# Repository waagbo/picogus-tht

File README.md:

# PicoGUS THT

PicoGUS is a Raspberry Pi Pico based ISA sound card for DOS and Win9x retro computers
It is a highly versatile clone card that provides near perfect emulation of the Gravis Ultrasound, Sound Blaster-series, AdLib, Tandy 3-voice and CMS/Game Blaster.

Additional features like CD-ROM (Panasonic MKE), MPU-401 and USB game controllers build further on the cards versatility and the wavetable header will further extend the capacity with a card like [X2GS from Serdaco](https://serdashop.com/products/x2gs-te) to get the original Roland magic or even a [WavetablePi](https://github.com/scrapcomputing/WavetablePiHoriz) for the ultimate all-in-one experience for MS-DOS games. 

**PicoGUS THT is a through-hole conversion of the [PicoGUS project](https://github.com/polpo/picogus).**<br />
The conversion introduces through-hole components where possible in addition to embedding new features and ideas while still keeping the card compatible with the upstream project. The design goal is to make the project be easier to solder by hand as well as giving it a higher level of retro asthetics.

PicoGUS THT exists in multiple variants based on different PicoGUS revisions. Each variant is found in their separate folder (or branch if still experimental). The different *hw* designs feature additional documentation including ready to order BOM CSVs in their respective *docs* folders.

The designs still have some TSSOP SMD chips as they do not have THT equivalents, namely the two *SN74CB3T3257PWR* level shifters (U3/U4) as well as the PCM510xA DAC. PicoGUS THT features a redesigned footprint to ease debugging in case something goes wrong.

**Note!** The hardware revisions are intentionally kept aligned with the *major* revision as the original PicoGUS boards. This is done to indicate hardware feature compatibility and to prevent confusion in case of any future major revisions of the original PicoGUS design.

### Version 1.3

This version is an extension of the PicoGUS 1.2 design while implementing the *wavetable header* with manual volume control from the *hw-hand386* branch. Together with the addition of a full size USB-A connector accessible from the computers backside this card is now a real competitor to the v2.0 SMD design.

In addition, the THT boards have also been slightly resized to optimize for component placement and JCLPCB-pricing.
The v1.3.2 has been successfully built by hand and the following features have been tested and verified.
The following features have been tested and verified.
* [x] Card Assembly ➔ OK, with minor adjustments to DigiKey BOM.
* [x] Flash, boot and detect card ➔ OK (v4.2.0-beta2).
* [x] Audio Playback ➔ OK (v4.2.0-beta2, SB Mode).
* [x] MIDI Playback (Wavetable Connector) ➔ OK (WavetablePi)
* [ ] MIDI Playback (External 3.5mm Jack)
* [x] USB-A Connector (Both CD-ROM and experimental PGDFS filesystem) ➔ OK

Assembly should be *EASY to MEDIUM* with the appropriate quality tools and consumables and a good project for beginners that want a little more challenge. Here is a list of recommended supplies with some personal recommendations:
* [Low Temperature Solder Paste](https://www.digikey.com/en/products/detail/chip-quik-inc/NC191LTA10/13531404) for easy soldering of SMD components.
* [Flux](https://www.digikey.com/en/products/detail/chip-quik-inc/NC191-2CC6/11480375) as it makes solder behave like magic when you need it the most.
* [Solder Wick](https://www.digikey.com/en/products/detail/chemtronics/SW14035/5177685) as it will help you when flux can't. Remember to **NEVER** pull a stuck wick.
* [Soldering Iron with J-Tip (Alientek T90B)](https://www.aliexpress.com/item/1005010015046346.html) will make the SMD components a breeze to solder. 
* [Tweezers](https://www.aliexpress.com/item/1005007298021096.html) for handling the SMD components.
* Digital Microscope of decent quality from AliExpress is very useful for visual inspection of SMD chips.
* Multimeter with good continuity tester.

#### User Build Gallery
|<br>waagbo|<br>|<br>|<br>|
|-|-|-|-|
| | | | |

### Version 2.1

This is an experimental extension of the PicoGUS 2.0 SMD design, made possible using a Waveshare Core2350B board to free enough I/O ports for the 2.0 feature set. This is still in the design phase.
<br/>

### Experimental Firmware
We have added experimental features that adds upon community ideas on top of the original firmware and software components. The features are submitted as Pull Requests to the original PicoGUS repository as well but there is no guarantee that they will ever be included in the official software releases:
* DFS drive support inspired by PicoMEM so the USB drive can be accessed from MS-DOS.
* CD images in a `CDROM` folder on the USB drive.
* A web page on boards with a Pico W or Pico 2 W: status, volumes, settings, mode switching, mt32-pi control and firmware updates from a browser.

The experimental features live on their own branches and are built into a separate *experimental* set of firmware and DOS tools next to the regular one, see [sw/experimental](sw/experimental/README.md).

### RP2350 Firmware
The firmware builds for the RP2350 as well as the RP2040, from the same source: for the v1.x boards with a Raspberry Pi Pico 2 (W) instead of a Pico (W), and for the v2.1 board's Core2350B module. Releases contain the firmware for both microcontrollers. See [RP2350 support](sw/docs/rp2350.md) for the firmware files, how to build them and what is left to test on hardware.

<br/>

**A big thank you to [Ian Scott (polpo)](https://github.com/polpo/) for the PicoGUS design and his contributions to the retro community.**<br/>**May his work set an example for future open-source hardware projects.**

--<br/>
Vidar Waagbø, Retro City AS

## PicoGUS

The original PicoGUS project is found at [polpo/pigocus](https://github.com/polpo/picogus) or www.picogus.com.<br/>
Here are the original README.md to give some more information about the great features of the PicoGUS:

ISA sound card and CD-ROM drive emulation on the Raspberry Pi Pico's RP2040 microcontroller. PicoGUS can emulate:

* [Gravis Ultrasound (GUS)](https://en.wikipedia.org/wiki/Gravis_Ultrasound) - the primary focus of PicoGUS, hence the name
* [Sound Blaster 16](https://en.wikipedia.org/wiki/Sound_Blaster_16) (OPL3) / [Sound Blaster Pro 2](https://en.wikipedia.org/wiki/Sound_Blaster#Sound_Blaster_Pro_2,_CT1600) (OPL3) / [AdLib](https://en.wikipedia.org/wiki/Ad_Lib,_Inc.) (OPL2)
* [MPU-401 (with intelligent mode)](https://en.wikipedia.org/wiki/MPU-401) - outputs MIDI data on 3.5mm MIDI TRS connector
* [Tandy 3-voice](http://www.vgmpf.com/Wiki/index.php?title=Tandy_3_Voice)
* [CMS/Game Blaster](http://nerdlypleasures.blogspot.com/2012/10/all-you-ever-wanted-to-know-about.html)
* [Game port joystick](https://en.wikipedia.org/wiki/Game_port)
* [Panasonic/MKE CD-ROM](https://en.wikipedia.org/wiki/Panasonic_CD_interface)

Current status: perpetual beta! See the [main wiki page](https://github.com/polpo/picogus/wiki) for current status and the [compatibility list](https://github.com/polpo/picogus/wiki/Compatibility-list) for support status of various DOS programs and other system compatibility notes. This project has a heavy demoscene focus due to the GUS's history so that's what I've concentrated on, but GUS support in games is very good to excellent.

Want to buy a PicoGUS? Fully assembled PicoGUS 2.0 sound cards are available from these sources, all of whom ship worldwide:

* [Joe's Computer Museum Shop](https://jcm-1.com/product/picogus-v2/) - in US 🇺🇸
* [Serdashop](https://www.serdashop.com/PicoGUS) - in EU 🇪🇺
* [Flamelily IT](https://shop.flamelily.co.uk/picogus) - in UK 🇬🇧

Want to make your own PicoGUS? See the [build guide](https://github.com/polpo/picogus/wiki/Building-your-PicoGUS). Note that the more DIY friendly v1.1.1 hardware has some documented issues with reset – a forthcoming v1.2 revision will fix these issues. **Important caveat**: due to the specs of the Pico, assumptions made by programs written to use the GUS, the imprecise nature of emulation, and the varying specs of retro DOS PC hardware, some things will likely never be perfect. **This is still a work in progress.**

Have a PicoGUS and want to use it? See the [configuring and using your PicoGUS guide](https://github.com/polpo/picogus/wiki/Configuring-and-using-your-PicoGUS).

Want to support PicoGUS? I have a limited number of machines to test PicoGUS in and donating either money or motherboards would be greatly appreciated and help increase the compatibility of PicoGUS.

You can donate via [PayPal](https://paypal.me/ianpolpo) or Ko-Fi: 

See/hear PicoGUS in action on YouTube:

Videos by others:

My videos:

## Open Source Credits

* [Raspberry Pi Pico C/C++ SDK](https://github.com/raspberrypi/pico-sdk)
* `pico_audio_i2s` from [pico-extras](https://github.com/raspberrypi/pico-extras)
* `stdio_async_uart` from [PicoCart64](https://github.com/kbeckmann/PicoCart64)
* `gus-x.cpp` adapted from [DOSBox-X](https://github.com/joncampbell123/dosbox-x)
* OPL/AdLib emulation from [rp2040-doom](https://github.com/kilograham/rp2040-doom) (based on [emu8950](https://github.com/digital-sound-antiques/emu8950))
* MPU-401 emulation adapted from [HardMPU](https://github.com/ab0tj/HardMPU) and [DOSBox-X](https://github.com/joncampbell123/dosbox-x)
* Tandy 3-voice emulation based on code contributed by [Aaron Giles](https://aarongiles.com/), adapted from [DREAMM](https://aarongiles.com/dreamm/) 
* CMS emulation based on code contributed by [Aaron Giles](https://aarongiles.com/), adapted from [DREAMM](https://aarongiles.com/dreamm/)
* USB support uses [TinyUSB](https://github.com/hathach/tinyusb) and [tusb_xinput](https://github.com/Ryzee119/tusb_xinput) with USB mass storage improvements by rppicomidi and wbcbz7.
* FAT drive support by [FatFS](https://elm-chan.org/fsw/ff/)

## License

The hardware portions of this repository (hw/ directory) are licensed under the CERN OHL version 2, permissive.

The software portions of this repository (sw/, pgusinit/ directories) as a collection are licensed under the GNU GPL version 2. Some files are individually dual-licensed under BSD or MIT licenses – see the license in the file headers for details.

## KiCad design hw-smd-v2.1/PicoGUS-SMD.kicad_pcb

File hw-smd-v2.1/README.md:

# PicoGUS SMD v2.1 – the THT v2.1 card with surface-mount parts

The SMD counterpart of [PicoGUS THT v2.1](../hw-tht-v2.1/README.md), in the way [`hw-smd`](../hw-smd/README.md) is the
SMD counterpart of THT v1.3. It is **the same circuit with the same reference designators and the same nets**, so the
THT v2.1 README describes how it works and the same firmware runs on it (`core2350.uf2`, and `pg-ne2k-v21.uf2` with
the radio module). Only the packages change.

* Same card: the 102.0 × 99.95 mm outline, the bracket-side connectors and tab holes of THT v2.1, 4 layers.
* **Same Core2350B arrangement**: the Waveshare Core2350B2 module on four 2x8 sockets, same footprint and same place.
* **Parts picked for soldering by hand**: 0805 resistors and capacitors on KiCad's hand-solder lands (longer pads),
  SOIC (1.27 mm pitch) wherever the chip exists as SOIC, and everything on the front. Nothing is on the back.
* The radio module (U14) and the experimental boot ROM (U15–U17) of THT v2.1 are included, and optional as there.
  The boot ROM's flash keeps its through-hole socket, and as on THT v2.1.1 it can be written in the card: see
  [Boot ROM socket](#boot-rom-socket).
* **Every joint can be made with a soldering iron.** That rules parts out whose leads hide under the body.

> **Status: draft for placement review. The schematic is done; the board has every part placed and labelled but is
> NOT routed. Not built, not tested.**
> The files say **v2.1.1** (2026-11-27), like THT v2.1.1 whose circuit they follow: the flash's write enable is on
> ISA's memory write strobe.
> Schematic: ERC gives the same messages as THT v2.1.1, and its netlist is identical to THT v2.1.1's (201 nets, 589
> pins, 102 parts; only footprints, values and part numbers differ). Board: 0 courtyard overlaps, 0 schematic parity
> issues, 398 connections still to route. The BOM has part numbers but no prices: see [BOM](#bom).
> The board is not in the Hardware workflow yet, because an unrouted board fails its DRC.

| File | What |
|---|---|
| `PicoGUS-SMD.kicad_pro/.kicad_sch/.kicad_pcb/.kicad_dru` | KiCad **10** project. The board is the THT v2.1 board (outline, stackup, plane zones, logo, edge connector, connectors and modules in place) with the SMD parts placed and no tracks |
| `audio.kicad_sch`, `mixer.kicad_sch`, `bootrom.kicad_sch` | The DAC, line-out mixer and boot ROM sheets of THT v2.1 with SMD footprints |
| `PicoGUS-SMD-schematic.pdf` | Schematic PDF |
| `docs/BOM-SMD.csv` | BOM with part numbers, no prices yet: see [BOM](#bom) |
| `docs/renders/` | Render of the placement |
| `tools/gen_tssop20_handsolder.py` | Writes the footprint this board adds to the shared library (`hw-common/PiGUS library.pretty`): the TSSOP-20 with hand-solder toes and no test pads |

## What changed from THT v2.1

| Part | THT v2.1 | SMD v2.1 |
|---|---|---|
| U3 74AHC14, U4/U5 74AHC00, U6 74AHCT126 | DIP-14 | SOIC-14 |
| U7 74AHC244 | DIP-20 | SOIC-20 wide |
| U11 NE5532 | DIP-8 | SOIC-8 |
| U9 MCP1826S 3.3 V regulator | TO-220, lying | SOT-223 |
| U16 74HCT138, U17 74HCT153 (boot ROM) | TSSOP-16 on the back | SOIC-16 on the front |
| U10 PCM5100A | TSSOP-20 with hand-solder toes and a test pad per pin | the same toes, no test pads |
| Resistors | axial; four 0805 on the back | 0805 on the front; 0.1 % thin film in the audio path (R10, R11, R21–R26), 1 % thick film elsewhere |
| Capacitors up to 2.2 µF | radial ceramic | 0805: X7R, and C0G for the DAC filter (C21, C22) and the mixer feedback (C24, C25) |
| 10 µF (C11–C13, C17, C47) | radial ceramic | 1206 |
| 47 µF and 100 µF (C1, C28, C29, C38) | radial electrolytic | SMD can, 6.3 mm |
| C39–C42, 2.2 µF Waveblaster coupling | film | bipolar SMD electrolytic, 4 mm can (as `hw-smd` does for the same job) |
| FB1–FB4 | axial ferrite | 0805 ferrite bead |
| D2, D3 | 1N5819, DO-41 | B5819W, SOD-123 |
| D1 | 3 mm LED | 0805 LED |
| F1 | radial PTC | 1812 PTC |
| SW1, SW2 | 6 mm through-hole button | 6 mm SMD button |

Unchanged: U1/U2 (SN74CB3T3257) exist only as TSSOP and keep THT v2.1's footprint with hand-solder toes and a test
pad per pin; U13 (M62429L) is a SOIC-8 already. All connectors and headers stay through hole, as do the module
sockets and the PLCC-32 socket of the boot ROM. The radio module keeps its hand-solder lands.

## Placement

The connectors, the module, the DAC, the mixer and the power parts are where THT v2.1 has them. The logic and the
boot ROM are grouped differently, because the small packages allow it:

* **ISA logic** (U3, U4, U5, U6 and U7): a 2 × 2 block of the SOIC-14s in the centre of the card, between the DAC and
  the bus switches, with U7 below it. On THT v2.1 the DIPs fill a column down the left edge, far from the edge
  connector pins, the jumper block and the module they connect. Measured as the straight-line length of the
  connections of these five chips (shortest tree per net, supplies left out):

  | Arrangement | Length | |
  |---|---|---|
  | Column on the left, as on THT v2.1 | 1773 mm | |
  | The same column with the chips in another order or turned 180° | 1766 mm at best | turning or reordering gains nothing |
  | The column closed up at its lower end (capacitors beside the chips) | 1690 mm | −5 % |
  | **Block in the centre (this placement)** | **1455 mm** | **−18 %** |

  For all signal nets of the card that is 4621 mm before and 4367 mm now. Each chip is turned so that its supply
  pin is at the bottom right, and its 0.1 µF capacitor stands right of it at that pin; that orientation costs 38 mm
  against the best one. The pull-ups and the pull-down (R5, R18, R1) stand left of the block. The left third of the
  card under the Waveblaster header is empty now.
* **Boot ROM**, bottom left: the flash socket where THT v2.1 has it, the address select U17 above it and the decoder
  U16 right of it.
* **Power**: the regulator U9 with its input and output capacitors against its pins, then the two supply diodes in a
  row that ends at the module's supply pin.
* **DAC**: see [DAC capacitors](#dac-capacitors). The AVDD bulk capacitor C38 is next to the bead that feeds AVDD
  (on THT v2.1 it is beside the mixer).
* **Mixer**: the feedback resistor and capacitor of each channel beside the op-amp pins they connect, the input
  resistors below them, the ±12 V filters above and below.
* **Waveblaster volume**: U13 is turned a quarter so both channels face the mixer, and all four coupling capacitors
  are at the chip. On THT v2.1 the two input capacitors are more than 30 mm away, near the header, which leaves a
  long high-impedance track. The input pull-downs R31/R32 moved here with them.
* The analogue parts stay inside THT v2.1's AGND and AVDD plane islands, which are unchanged; the logic block is
  outside them.

Neighbouring parts have at least 0.55 mm between their pads. Every part has its reference on the silkscreen beside
it: 0.8 mm text, 1.0 mm for the chips. The exceptions have no reference: the two buttons, which carry `RUN` and
`BOOTSEL`, J2 and J4 (`SWD`, `UART`), the edge connector and the mounting holes. The silkscreen check finds no new
overlap: what it reports, the divider line at J3 and U12's corner mark on its pin 1, is on THT v2.1 as well.

### DAC capacitors

With a test pad per pin, as on THT v2.1, the capacitors of U10 stood 2.3 to 5.3 mm from their pins, beyond the test
pads. Here U10 is on the same hand-solder toes without the test pads, and the capacitors are placed in the order in
which they matter:

| Capacitor | Pin of U10 | Where | Pad to pad |
|---|---|---|---|
| C18, charge pump flying capacitor | 2 and 4 (CAPP, CAPM) | across the two pins, straight above them | 0.7 mm each (was 2.3 and 4.7) |
| C16, charge pump supply | 1 (CPVDD) | at pin 1's corner of the package | 1.3 mm (was 4.8) |
| C15, analogue supply | 8 (AVDD) | straight above the pin, with the 10 µF C17 beside it | 0.7 mm (was 5.3) |
| C19, negative rail | 5 (VNEG) | behind C18 | 2.9 mm (was 2.3) |
| C20, internal regulator | 18 (LDOO) | straight below the pin | 0.7 mm (was 2.5) |
| C14, digital supply | 20 (DVDD) | at pin 20's corner | 1.3 mm (was 2.5) |

Pins 1 to 5 are 0.65 mm apart and an 0805 is 2 mm wide, so not every capacitor can be at its pin: the flying
capacitor and the supplies come first, and C19 sits one row out. The two outputs (pins 6 and 7) leave between C15
and C18 to their filter (R10/C21, R11/C22) 6 mm away; they are not sensitive to that length. The ground pins (3, 9
and the strapped pins) are meant to go to vias under the package when the board is routed, because the capacitor
pads cover the space above them.

### Boot ROM socket

The flash (U15, PLCC-32) stays in THT v2.1's through-hole socket, because every joint on this board has to be
possible with a soldering iron. What was looked at (maker drawings read 2026-11-27):

* **Surface-mount PLCC-32 sockets**: Amphenol FCI 69802, Assmann A-CCS 032-Z-SM, Mill-Max 940, Kycon SMPX-32LCC,
  Preci-Dip 540, 3M 8432, CNC Tech 232-32, Connfly DS1032 and Samtec PLCC-032 all turn their solder tails inwards
  under the housing, 2 to 3 mm inside its outer wall. None with leads on the outside was found.
* **Surface-mount DIP-32 sockets with gull-wing leads** (Mill-Max 110-xx-632-41-105000, Preci-Dip
  110-87-632-41-105101, Samtec ICF-632-x-O) can be soldered by hand and would take the DIP version of the same
  flash. They are 40.6 mm long and about 21 mm over the pads, cost 6 to 23 US$ and were hardly in stock, so they
  are not used.

**The flash can be written in the card** (from v2.1.1, as on THT v2.1.1): its write enable (pin 31) is on ISA's
memory write strobe SMEMW (edge connector pin B11) instead of +5 V. By the SST39SF010A datasheet (DS20005022) the
chip writes from 5 V alone, its command addresses 5555h and 2AAAh use only A0–A14, so they lie inside the 32 KB
window, and A15/A16 tied low is allowed. XTIDECFG (r620 and later, "SST39SFx flash") and Lo-tech's FLASH utility
program this chip in a 32 KB window from DOS; see the THT v2.1 README for how. The chip's own three-byte unlock
sequence is the write protection: there is no jumper. **Not tested on a card.**

That makes it possible to leave the socket out and solder the flash itself: its J-leads on 1.27 mm pitch can be
soldered by hand. This board does not do that yet, because a soldered chip depends on the write path, and that has
not run on a card. A THT v2.1.0 card with the [two wires](../hw-tht-v2.1/docs/v2.1.0-flash-write-mod.md) has the
same circuit and can show it. An image that stops the PC during its start-up would not be the end of a soldered
chip: with BOOTSEL held while the PC starts, the module waits in its USB loader and R35/R36 keep the ROM switched
off; RUN, pressed once DOS is up, starts the firmware, which switches the ROM on again so it can be written anew
(from the schematic and the firmware source, not tried).

## BOM

`docs/BOM-SMD.csv` lists every part with manufacturer part number and DigiKey number. The column **Part number**
says where each line comes from:

* `as on THT v2.1` (18 lines): the same part as on the through-hole board, taken from its BOM.
* `hw-smd BOM (2026-09-29)` (21 lines): the part and its DigiKey number come from the checked BOM of `hw-smd`.
* `checked 2026-11-24` (12 lines): the parts that are new here, looked up on DigiKey's product page and, where the
  land pattern or the pin-out depends on it, in the manufacturer's datasheet. The Notes column says what was read.

Stock and prices were not looked at for any line, and there are no cart upload files yet: they come when the board
is routed.

Three things from the check that are easy to get wrong when ordering:

* **C38** is EEE-FK1E101**X**P (6.3 mm can). EEE-FK1E101P without the X is 8 mm and does not fit.
* **C39–C42** are UWP1**V**2R2MCL1GB (35 V, 4 mm can). The 50 V UWP1H2R2MCL1GB is 5 mm and does not fit. They are
  bipolar and fit either way round; the + mark on the board comes with KiCad's footprint and means nothing here.
* **U9**: the SOT-223 MCP1826S has the same pin order as the TO-220 of THT v2.1 (VIN, GND, VOUT, tab on GND).
  DigiKey sells MCP1826S-3302E/DB only in tubes; the BOM names the taped MCP1826ST-3302E/DB.

## Next

1. Review of the placement.
2. The flash soldered straight to the board in place of the socket, if that is wanted: see
   [Boot ROM socket](#boot-rom-socket).
3. Routing (4 layers, 0.2 mm tracks and clearances; the boot ROM corner should not need THT v2.1's 0.15 mm any more),
   DRC, then the Hardware workflow entry and JLCPCB files.
4. Prices, DigiKey and LCSC upload files.

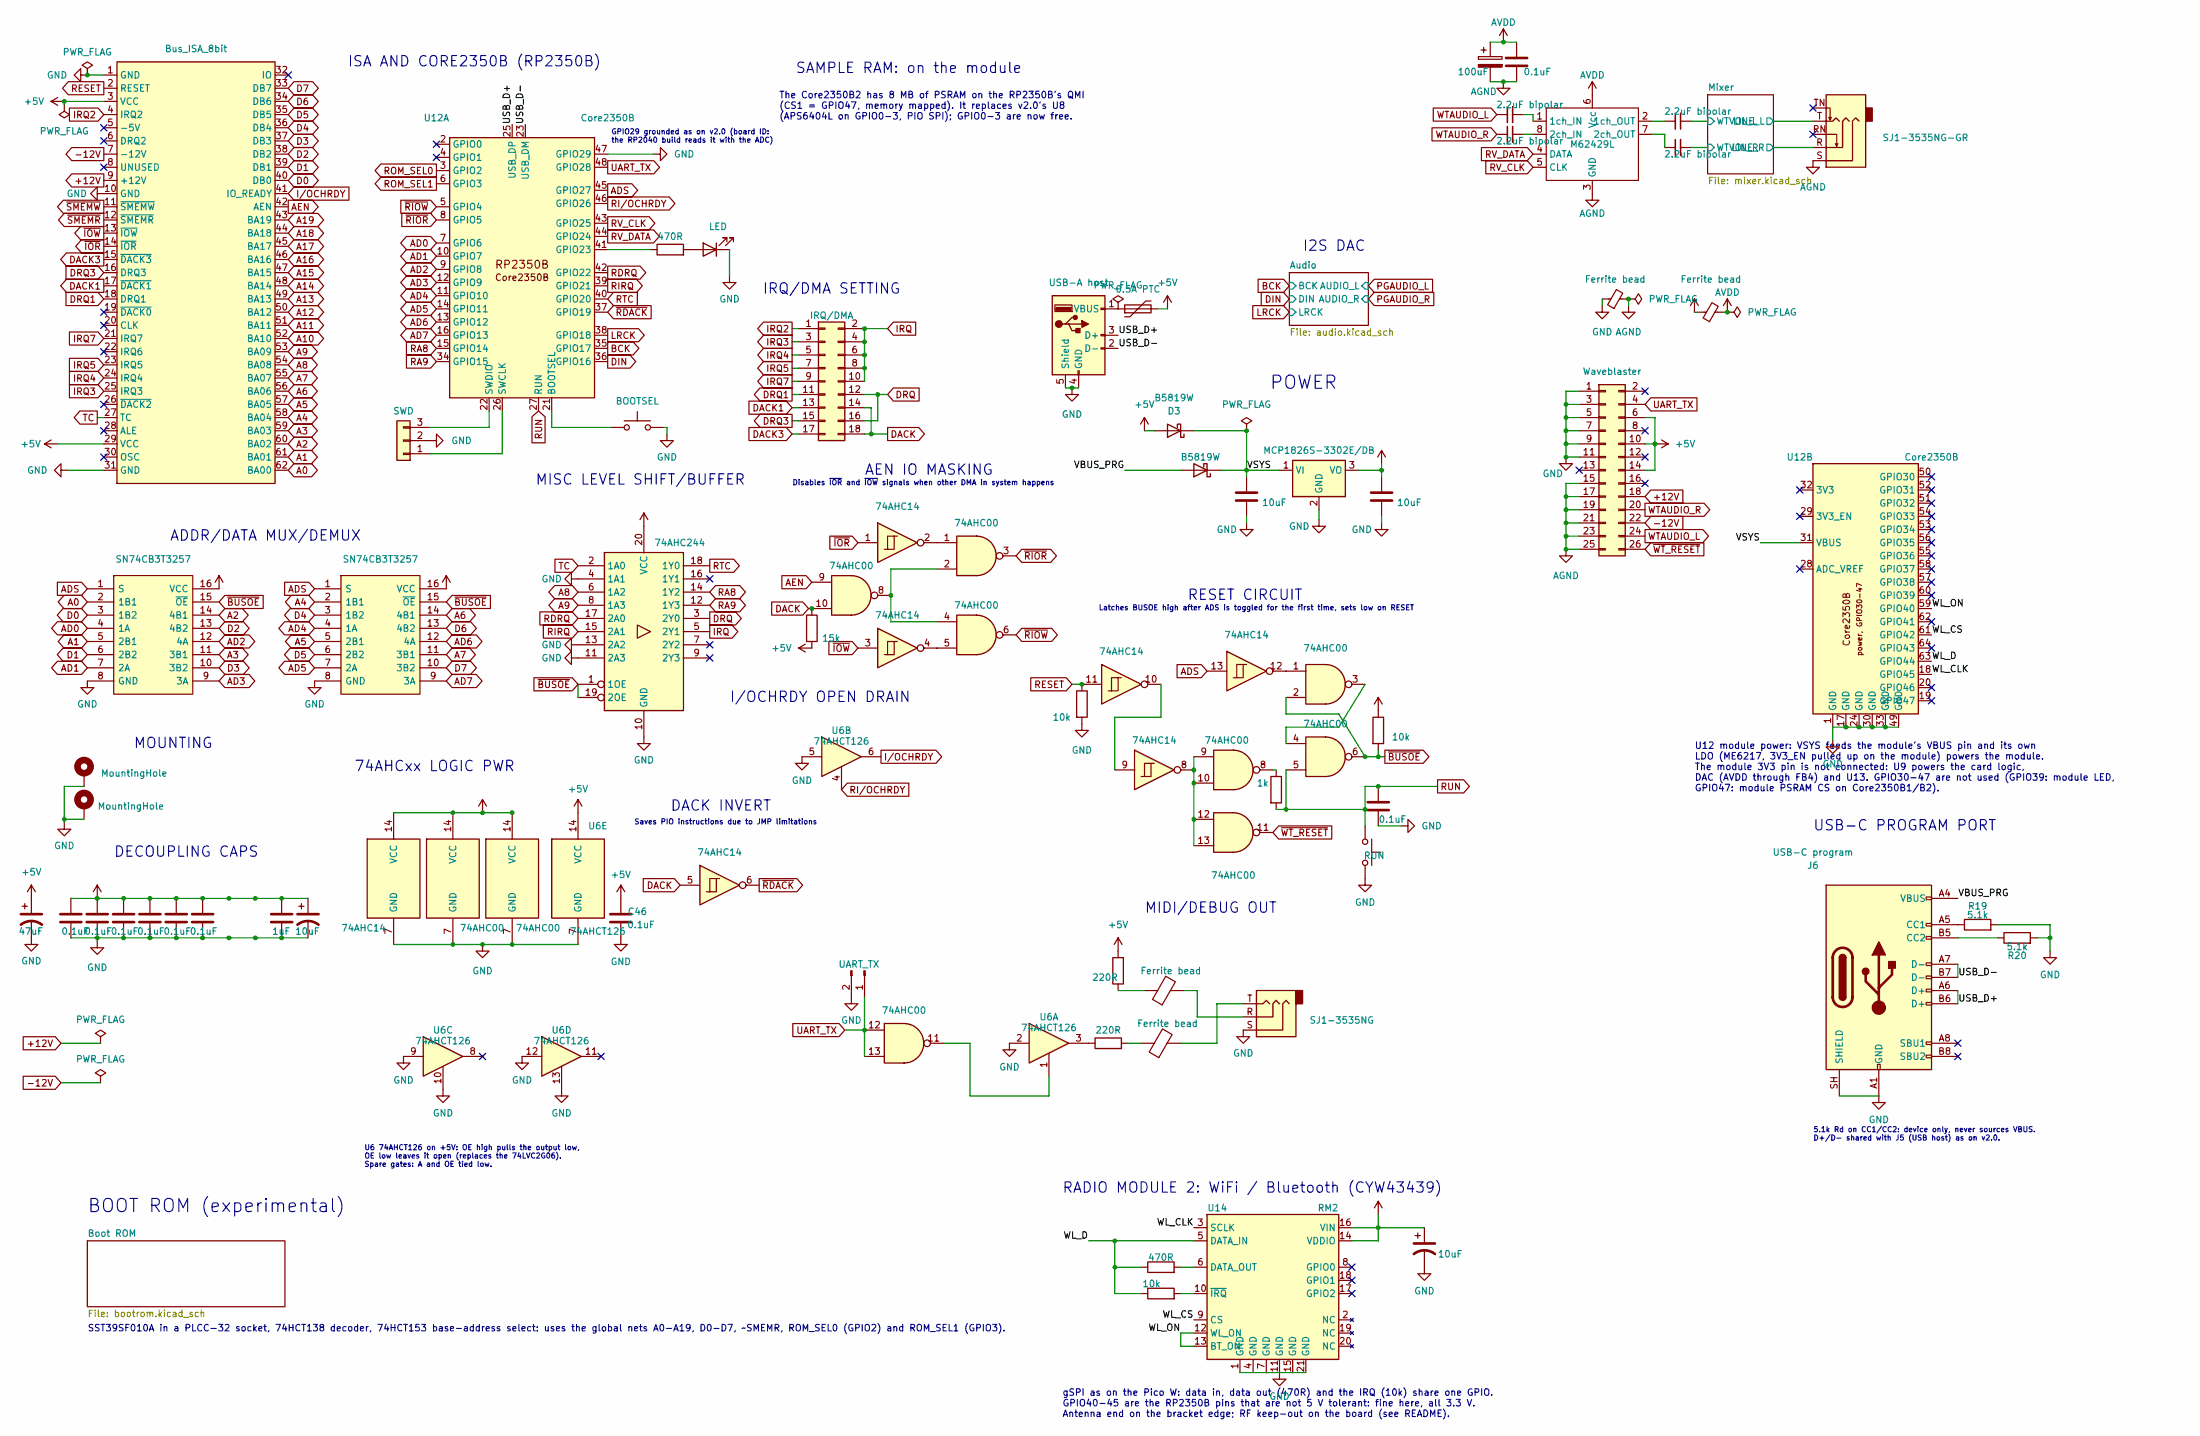
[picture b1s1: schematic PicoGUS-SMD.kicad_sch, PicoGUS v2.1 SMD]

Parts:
C1: 47uF; CP_Elec_6.3x7.7; MPN EEE-FK1V470P; DigiKey PCE3842CT-ND
C2, C3, C4, C5, C6, C7, C23, C45, C46: 0.1uF; C_0805_2012Metric_Pad1.18x1.45mm_HandSolder; MPN CL21B104KBCNNNC; DigiKey 1276-1003-1-ND
C10: 1uF; C_0805_2012Metric_Pad1.18x1.45mm_HandSolder; MPN C2012X7R1H105K125AB; DigiKey 445-7547-1-ND
C11, C12, C13, C47: 10uF; C_1206_3216Metric_Pad1.33x1.80mm_HandSolder; MPN CL31A106KAHNNNE; DigiKey 1276-1075-1-ND
C38: 100uF; CP_Elec_6.3x7.7; MPN EEE-FK1E101XP; DigiKey PCE3797CT-ND
C39, C40, C41, C42: 2.2uF bipolar; CP_Elec_4x5.4; MPN UWP1V2R2MCL1GB; DigiKey 493-9836-1-ND
D1: LED; LED_0805_2012Metric_Pad1.15x1.40mm_HandSolder; MPN LTST-C170KGKT; DigiKey 160-1414-1-ND
D2, D3: B5819W; D_SOD-123; MPN B5819W; DigiKey 5399-B5819WCT-ND
F1: 0.5A PTC; Fuse_1812_4532Metric_Pad1.30x3.40mm_HandSolder; MPN MF-MSMF050-2; DigiKey MF-MSMF050-2CT-ND
FB1, FB2, FB3, FB4: Ferrite bead; L_0805_2012Metric_Pad1.05x1.20mm_HandSolder; MPN BLM21AG102SN1D; DigiKey 490-1041-1-ND
H1, H2: MountingHole; MountingHole_3.2mm_M3_Pad
J1: Bus_ISA_8bit; BUS_PC_chamfer
J2: SWD; PinHeader_1x03_P2.54mm_Vertical; MPN PREC040SAAN-RC; DigiKey S1012EC-40-ND
J3: IRQ/DMA; PinHeader_2x09_P2.54mm_Vertical; MPN 10129381-918001BLF; DigiKey 609-10129381-918001BLF-ND
J4: UART_TX; PinHeader_1x02_P2.54mm_Vertical; MPN PREC040SAAN-RC; DigiKey S1012EC-40-ND
J5: USB-A host; USB_A_Molex_67643_Horizontal_ShieldPin5; MPN 0676430910; DigiKey WM4993-ND
J6: USB-C program; USB_C_Receptacle_GCT_USB4085; MPN USB4085-GF-A; DigiKey 2073-USB4085-GF-ACT-ND
J7: SJ1-3535NG; Jack_3.5mm_CUI_SJ1-3535NG_Horizontal; MPN SJ1-3535NG; DigiKey CP1-3535NG-ND
J8: Waveblaster; Wavetable_NoMountingHoles; MPN PEC13DAAN; DigiKey 35-PEC13DAAN-ND
J9: SJ1-3535NG-GR; Jack_3.5mm_CUI_SJ1-3535NG_Horizontal; MPN SJ1-3535NG-GR; DigiKey CP1-3535NG-GR-ND
R1, R5, R34: 10k; R_0805_2012Metric_Pad1.20x1.40mm_HandSolder; MPN RC0805FR-0710KL; DigiKey 311-10.0KCRCT-ND
R2, R3: 220R; R_0805_2012Metric_Pad1.20x1.40mm_HandSolder; MPN RC0805FR-07220RL; DigiKey 311-220CRCT-ND
R4: 1k; R_0805_2012Metric_Pad1.20x1.40mm_HandSolder; MPN RC0805FR-071KL; DigiKey 311-1.00KCRCT-ND
R13, R33: 470R; R_0805_2012Metric_Pad1.20x1.40mm_HandSolder; MPN RC0805FR-07470RL; DigiKey 311-470CRCT-ND
R18: 15k; R_0805_2012Metric_Pad1.20x1.40mm_HandSolder; MPN RC0805FR-0715KL; DigiKey 311-15.0KCRCT-ND
R19, R20: 5.1k; R_0805_2012Metric_Pad1.20x1.40mm_HandSolder; MPN RC0805FR-075K1L; DigiKey 311-5.10KCRCT-ND
SW1: BOOTSEL; SW_SPST_B3S-1000; MPN B3S-1000P; DigiKey SW836CT-ND
SW2: RUN; SW_SPST_B3S-1000; MPN B3S-1000P; DigiKey SW836CT-ND
U1, U2: SN74CB3T3257; TSSOP-16_4.4x5mm_P0.65mm_HandSolder_TestPads; Manufacturer_Part_Number 74FST3257DR2G; Mouser Part Number 863-74FST3257DR2G
U3: 74AHC14; SOIC-14_3.9x8.7mm_P1.27mm; MPN 74AHC14S14-13; DigiKey 31-74AHC14S14-13CT-ND
U4, U5: 74AHC00; SOIC-14_3.9x8.7mm_P1.27mm; MPN SN74AHC00DR; DigiKey 296-4509-1-ND
U6: 74AHCT126; SOIC-14_3.9x8.7mm_P1.27mm; MPN SN74AHCT126DR; DigiKey 296-4658-1-ND
U7: 74AHC244; SOIC-20W_7.5x12.8mm_P1.27mm; MPN SN74AHC244DWR; DigiKey 296-1096-1-ND
U9: MCP1826S-3302E/DB; SOT-223-3_TabPin2; MPN MCP1826ST-3302E/DB; DigiKey MCP1826ST-3302E/DBCT-ND
U12: Core2350B; Waveshare_Core2350B; MPN Core2350B2; DigiKey not stocked: waveshare.com SKU 31690 (B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
U13: M62429L; SOIC-8_3.9x4.9mm_P1.27mm; MPN M62429L.TR; DigiKey not stocked: LCSC only (DigiKey marketp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
U14: RM2; RaspberryPi_RM2_HandSolder; MPN RMC20452T

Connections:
+3V3: C2.1, C3.1, C4.1, C5.1, C6.1, C7.1, C10.1, C11.1, C13.1, C47.1, FB4.1, R5.1, U1.16 (VCC), U2.16 (VCC), U3.14 (VCC), U4.14 (VCC), U5.14 (VCC), U7.20 (VCC), U9.3 (VO), U14.14 (VDDIO), U14.16 (VIN); also elsewhere on the board
+5V: C1.1, C46.1, D3.2 (A), F1.2, J1.3 (VCC), J1.29 (VCC), J8.6, J8.10, J8.14, R3.2, R18.2, U6.14 (VCC); also elsewhere on the board
+12V: J1.9 (+12V), J8.18; also elsewhere on the board
-12V: J1.7 (-12V), J8.22; also elsewhere on the board
/Mixer/LINE_L: J9.T; also elsewhere on the board
/Mixer/LINE_R: J9.R; also elsewhere on the board
/Mixer/WTVOL_L: C41.2; also elsewhere on the board
/Mixer/WTVOL_R: C42.2; also elsewhere on the board
/USB_D+: J5.3 (D+), J6.A6 (D+), J6.B6 (D+), U12.25 (USB_DP)
/USB_D-: J5.2 (D-), J6.A7 (D-), J6.B7 (D-), U12.23 (USB_DM)
/VBUS_PRG: D2.2 (A), J6.A4 (VBUS), J6.A9 (VBUS), J6.B4 (VBUS), J6.B9 (VBUS)
/VSYS: C12.1, D2.1 (K), D3.1 (K), U9.1 (VI), U12.31 (VBUS)
/WL_CLK: U12.18 (GP45), U14.3 (SCLK)
/WL_CS: U12.61 (GP42), U14.9 (CS)
/WL_D: R33.1, R34.1, U12.63 (GP44), U14.5 (DATA_IN)
/WL_ON: U12.59 (GP40), U14.12 (WL_ON), U14.13 (BT_ON)
A0: J1.62 (BA00), U1.2 (1B1); also elsewhere on the board
A1: J1.61 (BA01), U1.5 (2B1); also elsewhere on the board
A2: J1.60 (BA02), U1.14 (4B1); also elsewhere on the board
A3: J1.59 (BA03), U1.11 (3B1); also elsewhere on the board
A4: J1.58 (BA04), U2.2 (1B1); also elsewhere on the board
A5: J1.57 (BA05), U2.5 (2B1); also elsewhere on the board
A6: J1.56 (BA06), U2.14 (4B1); also elsewhere on the board
A7: J1.55 (BA07), U2.11 (3B1); also elsewhere on the board
A8: J1.54 (BA08), U7.6 (1A2); also elsewhere on the board
A9: J1.53 (BA09), U7.8 (1A3); also elsewhere on the board
A10: J1.52 (BA10); also elsewhere on the board
A11: J1.51 (BA11); also elsewhere on the board
A12: J1.50 (BA12); also elsewhere on the board
A13: J1.49 (BA13); also elsewhere on the board
A14: J1.48 (BA14); also elsewhere on the board
A15: J1.47 (BA15); also elsewhere on the board
A16: J1.46 (BA16); also elsewhere on the board
A17: J1.45 (BA17); also elsewhere on the board
A18: J1.44 (BA18); also elsewhere on the board
A19: J1.43 (BA19); also elsewhere on the board
AD0: U1.4 (1A), U12.7 (GP6)
AD1: U1.7 (2A), U12.10 (GP7)
AD2: U1.12 (4A), U12.9 (GP8)
AD3: U1.9 (3A), U12.12 (GP9)
AD4: U2.4 (1A), U12.11 (GP10)
AD5: U2.7 (2A), U12.14 (GP11)
AD6: U2.12 (4A), U12.13 (GP12)
AD7: U2.9 (3A), U12.16 (GP13)
ADS: U1.1 (S), U2.1 (S), U3.13, U12.45 (GP27)
AEN: J1.42 (AEN), U4.9
AGND: C23.2, C38.2, FB3.2, J8.15, J8.17, J8.19, J8.21, J8.23, J8.25, J9.S, U13.3 (GND); also elsewhere on the board
AVDD: C23.1, C38.1, FB4.2, U13.6 (Vcc); also elsewhere on the board
BCK: U12.35 (GP17); also elsewhere on the board
D0: J1.40 (DB0), U1.3 (1B2); also elsewhere on the board
D1: J1.39 (DB1), U1.6 (2B2); also elsewhere on the board
D2: J1.38 (DB2), U1.13 (4B2); also elsewhere on the board
D3: J1.37 (DB3), U1.10 (3B2); also elsewhere on the board
D4: J1.36 (DB4), U2.3 (1B2); also elsewhere on the board
D5: J1.35 (DB5), U2.6 (2B2); also elsewhere on the board
D6: J1.34 (DB6), U2.13 (4B2); also elsewhere on the board
D7: J1.33 (DB7), U2.10 (3B2); also elsewhere on the board
DACK: J3.14, J3.18, R18.1, U3.5, U4.10
DACK1: J1.17 (~DACK1), J3.13
DACK3: J1.15 (~DACK3), J3.17
DIN: U12.36 (GP16); also elsewhere on the board
DRQ: J3.12, J3.16, U7.3 (2Y0)
DRQ1: J1.18 (DRQ1), J3.11
DRQ3: J1.16 (DRQ3), J3.15
GND: C1.2, C2.2, C3.2, C4.2, C5.2, C6.2, C7.2, C10.2, C11.2, C12.2, C13.2, C45.2, C46.2, C47.2, D1.1 (K), FB3.1, H1.1, H2.1, J1.1 (GND), J1.10 (GND), J1.31 (GND), J2.2, J4.2, J5.4 (GND), J5.5 (Shield), J6.A1 (GND), J6.A12 (GND), J6.B1 (GND), J6.B12 (GND), J6.SH (SHIELD), J7.S, J8.1, J8.3, J8.5, J8.7, J8.9, J8.11, R1.2, R19.2, R20.2, SW1.2, SW2.2, U1.8 (GND), U2.8 (GND), U3.7 (GND), U4.7 (GND), U5.7 (GND), U6.2, U6.5, U6.7 (GND), U6.9, U6.10, U6.12, U6.13, U7.4 (1A1), U7.10 (GND), U7.11 (2A3), U7.13 (2A2), U9.2 (GND), U12.1 (GND), U12.17 (GND), U12.24 (GND), U12.30 (GND), U12.33 (GND), U12.47 (GP29), U12.49 (GND), U14.1 (GND), U14.4 (GND), U14.7 (GND), U14.11 (GND), U14.15 (GND), U14.21 (GND); also elsewhere on the board
IRQ: J3.2, J3.4, J3.6, J3.8, J3.10, U7.5 (2Y1)
IRQ2: J1.4 (IRQ2), J3.1
IRQ3: J1.25 (IRQ3), J3.3
IRQ4: J1.24 (IRQ4), J3.5
IRQ5: J1.23 (IRQ5), J3.7
IRQ7: J1.21 (IRQ7), J3.9
I/OCHRDY: J1.41 (IO_READY), U6.6
LRCK: U12.38 (GP18); also elsewhere on the board
unnamed: D1.2 (A), R13.2
unnamed: FB1.1, R2.2
unnamed: FB1.2, J7.T
unnamed: FB2.1, R3.1
unnamed: FB2.2, J7.R
unnamed: J2.1, U12.26 (SWCLK)
unnamed: J2.3, U12.22 (SWDIO)
unnamed: F1.1, J5.1 (VBUS)
unnamed: J6.A5 (CC1), R19.1
unnamed: J6.B5 (CC2), R20.1
unnamed: R2.1, U6.3
unnamed: R4.1, U5.8
unnamed: U3.2, U4.1
unnamed: U3.4, U4.5
unnamed: U3.8, U5.9, U5.10, U5.12, U5.13
unnamed: U3.9, U3.10
unnamed: U3.12, U5.1
unnamed: U4.2, U4.4, U4.8
unnamed: U4.11, U6.1
unnamed: U5.3, U5.4
unnamed: SW1.1, U12.21 (BOOTSEL)
unnamed: R13.1, U12.41 (GP23)
unnamed: C39.2, U13.1 (1ch_IN)
unnamed: C41.1, U13.2 (1ch_OUT)
unnamed: C40.2, U13.8 (2ch_IN)
unnamed: C42.1, U13.7 (2ch_OUT)
unnamed: R33.2, U14.6 (DATA_OUT)
unnamed: R34.2, U14.10 (nIRQ)
RA8: U7.14 (1Y2), U12.15 (GP14)
RA9: U7.12 (1Y3), U12.34 (GP15)
RDRQ: U7.17 (2A0), U12.42 (GP22)
RESET: J1.2 (RESET), R1.1, U3.11
RIRQ: U7.15 (2A1), U12.39 (GP21)
RI/OCHRDY: U6.4, U12.46 (GP26)
ROM_SEL0: U12.3 (GP2); also elsewhere on the board
ROM_SEL1: U12.6 (GP3); also elsewhere on the board
RTC: U7.18 (1Y0), U12.40 (GP20)
RUN: C45.1, R4.2, SW2.1, U5.5, U12.27 (RUN)
RV_CLK: U12.43 (GP25), U13.5 (CLK)
RV_DATA: U12.44 (GP24), U13.4 (DATA)
TC: J1.27 (TC), U7.2 (1A0)
UART_TX: J4.1, J8.4, U4.12, U4.13, U12.48 (GP28)
WTAUDIO_L: C39.1, J8.24; also elsewhere on the board
WTAUDIO_R: C40.1, J8.20; also elsewhere on the board
~BUSOE: R5.2, U1.15 (~OE), U2.15 (~OE), U5.2, U5.6, U7.1 (1OE), U7.19 (2OE)
~IOR: J1.14 (~IOR), U3.1
~IOW: J1.13 (~IOW), U3.3
~RDACK: U3.6, U12.37 (GP19)
~RIOR: U4.3, U12.8 (GP5)
~RIOW: U4.6, U12.5 (GP4)
~SMEMR: J1.12 (~SMEMR); also elsewhere on the board
~SMEMW: J1.11 (~SMEMW); also elsewhere on the board
~WT_RESET: J8.26, U5.11

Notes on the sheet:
Saves PIO instructions due to JMP limitations
5.1k Rd on CC1/CC2: device only, never sources VBUS. D+/D- shared with J5 (USB host) as on v2.0.
U6 74AHCT126 on +5V: OE high pulls the output low, OE low leaves it open (replaces the 74LVC2G06). Spare gates: A and OE tied low.
DECOUPLING CAPS
GPIO29 grounded as on v2.0 (board ID: the RP2040 build reads it with the ADC)
I2S DAC
USB-C PROGRAM PORT
Disables ~{IOR} and ~{IOW} signals when other DMA in system happens
Latches BUSOE high after ADS is toggled for the first time, sets low on RESET
MIDI/DEBUG OUT
MOUNTING
MISC LEVEL SHIFT/BUFFER
IRQ/DMA SETTING
U12 module power: VSYS feeds the module's VBUS pin and its own LDO (ME6217, 3V3_EN pulled up on the module) powers the module. The module 3V3 pin is not connected: U9 powers the card logic, DAC (AVDD through FB4) and U13. GPIO30-47 are not used (GPIO39: module LED, GPIO47: module PSRAM CS on Core23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
DACK INVERT
ADDR/DATA MUX/DEMUX
SAMPLE RAM: on the module
The Core2350B2 has 8 MB of PSRAM on the RP2350B's QMI (CS1 = GPIO47, memory mapped). It replaces v2.0's U8 (APS6404L on GPIO0-3, PIO SPI); GPIO0-3 are now free.
AEN IO MASKING
ISA AND CORE2350B (RP2350B)
POWER
RESET CIRCUIT
I/OCHRDY OPEN DRAIN
74AHCxx LOGIC PWR
RADIO MODULE 2: WiFi / Bluetooth (CYW43439)
gSPI as on the Pico W: data in, data out (470R) and the IRQ (10k) share one GPIO. GPIO40-45 are the RP2350B pins that are not 5 V tolerant: fine here, all 3.3 V. Antenna end on the bracket edge; RF keep-out on the board (see README).
BOOT ROM (experimental)
SST39SF010A in a PLCC-32 socket, 74HCT138 decoder, 74HCT153 base-address select: uses the global nets A0-A19, D0-D7, ~SMEMR, ROM_SEL0 (GPIO2) and ROM_SEL1 (GPIO3).

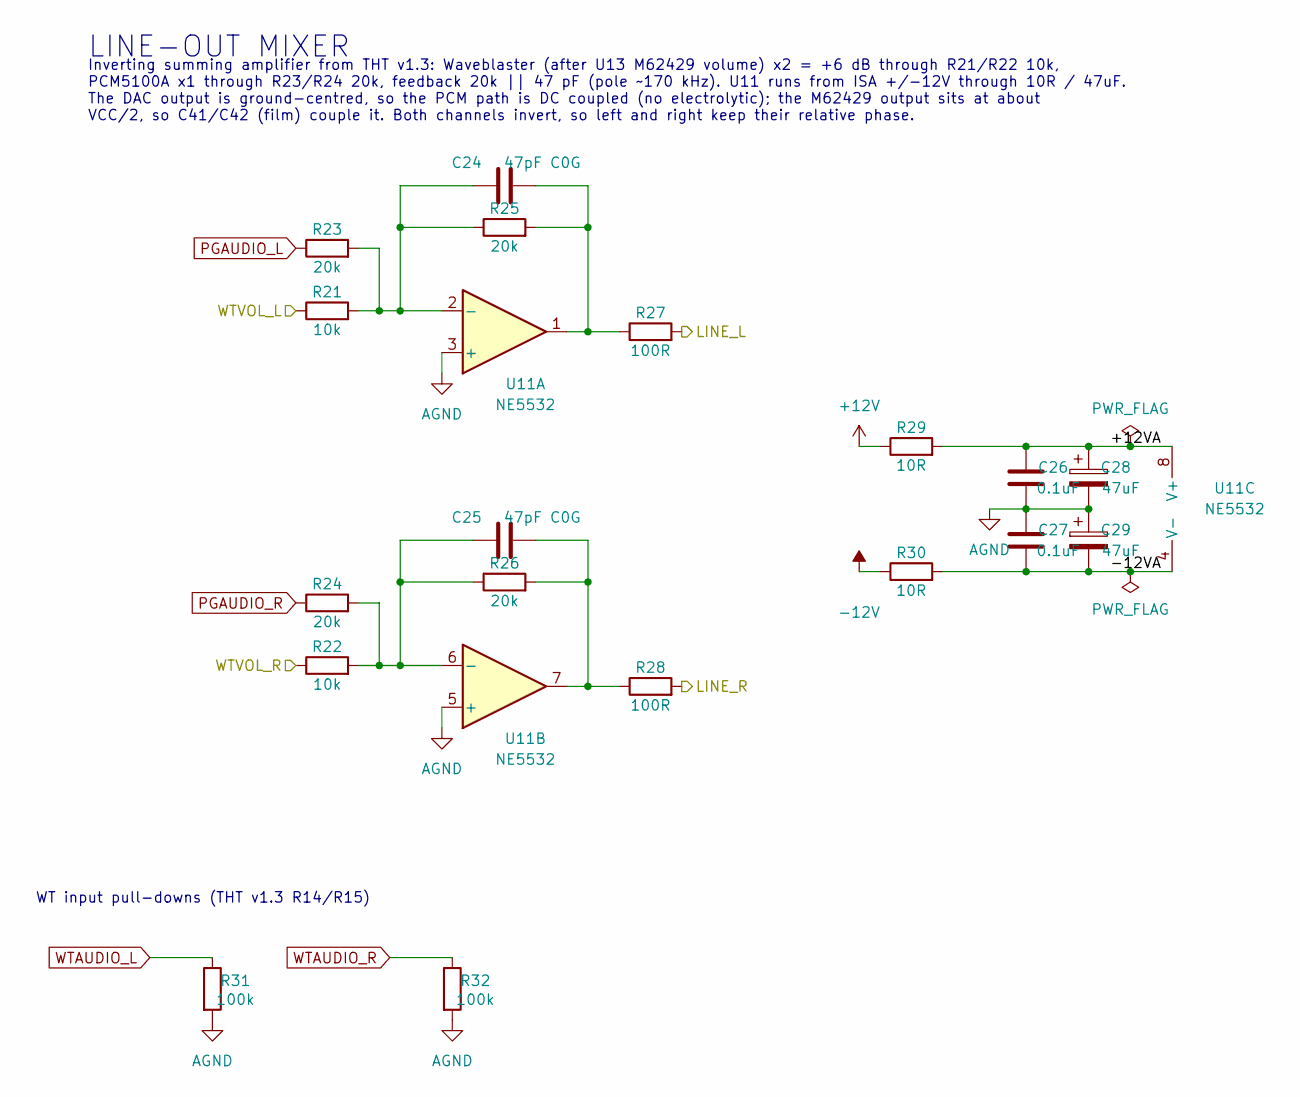
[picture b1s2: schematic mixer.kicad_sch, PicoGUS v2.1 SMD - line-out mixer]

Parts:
C24, C25: 47pF C0G; C_0805_2012Metric_Pad1.18x1.45mm_HandSolder; MPN CL21C470JC61PNC; DigiKey 1276-6521-1-ND
C26, C27: 0.1uF; C_0805_2012Metric_Pad1.18x1.45mm_HandSolder; MPN CL21B104KBCNNNC; DigiKey 1276-1003-1-ND
C28, C29: 47uF; CP_Elec_6.3x7.7; MPN EEE-FK1V470P; DigiKey PCE3842CT-ND
R21, R22: 10k; R_0805_2012Metric_Pad1.20x1.40mm_HandSolder; MPN RT0805BRD0710KL; DigiKey YAG1763CT-ND
R23, R24, R25, R26: 20k; R_0805_2012Metric_Pad1.20x1.40mm_HandSolder; MPN RT0805BRD0720KL; DigiKey YAG1823CT-ND
R27, R28: 100R; R_0805_2012Metric_Pad1.20x1.40mm_HandSolder; MPN RC0805FR-07100RL; DigiKey 311-100CRCT-ND
R29, R30: 10R; R_0805_2012Metric_Pad1.20x1.40mm_HandSolder; MPN RC0805FR-0710RL; DigiKey 311-10.0CRCT-ND
R31, R32: 100k; R_0805_2012Metric_Pad1.20x1.40mm_HandSolder; MPN RC0805FR-07100KL; DigiKey 311-100KCRCT-ND
U11: NE5532; SOIC-8_3.9x4.9mm_P1.27mm; MPN NE5532DR; DigiKey 296-13622-1-ND

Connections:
+12V: R29.1; also elsewhere on the board
-12V: R30.1; also elsewhere on the board
/Mixer/+12VA: C26.1, C28.1, R29.2, U11.8 (V+)
/Mixer/-12VA: C27.2, C29.2, R30.2, U11.4 (V-)
/Mixer/LINE_L: R27.2; also elsewhere on the board
/Mixer/LINE_R: R28.2; also elsewhere on the board
/Mixer/WTVOL_L: R21.1; also elsewhere on the board
/Mixer/WTVOL_R: R22.1; also elsewhere on the board
AGND: C26.2, C27.1, C28.2, C29.1, R31.2, R32.2, U11.3 (+), U11.5 (+); also elsewhere on the board
unnamed: C24.2, R25.2, R27.1, U11.1
unnamed: C25.2, R26.2, R28.1, U11.7
unnamed: C24.1, R21.2, R23.2, R25.1, U11.2 (-)
unnamed: C25.1, R22.2, R24.2, R26.1, U11.6 (-)
PGAUDIO_L: R23.1; also elsewhere on the board
PGAUDIO_R: R24.1; also elsewhere on the board
WTAUDIO_L: R31.1; also elsewhere on the board
WTAUDIO_R: R32.1; also elsewhere on the board

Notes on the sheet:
LINE-OUT MIXER
Inverting summing amplifier from THT v1.3: Waveblaster (after U13 M62429 volume) x2 = +6 dB through R21/R22 10k, PCM5100A x1 through R23/R24 20k, feedback 20k || 47 pF (pole ~170 kHz). U11 runs from ISA +/-12V through 10R / 47uF. The DAC output is ground-centred, so the PCM path is DC coupled (no e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
WT input pull-downs (THT v1.3 R14/R15)

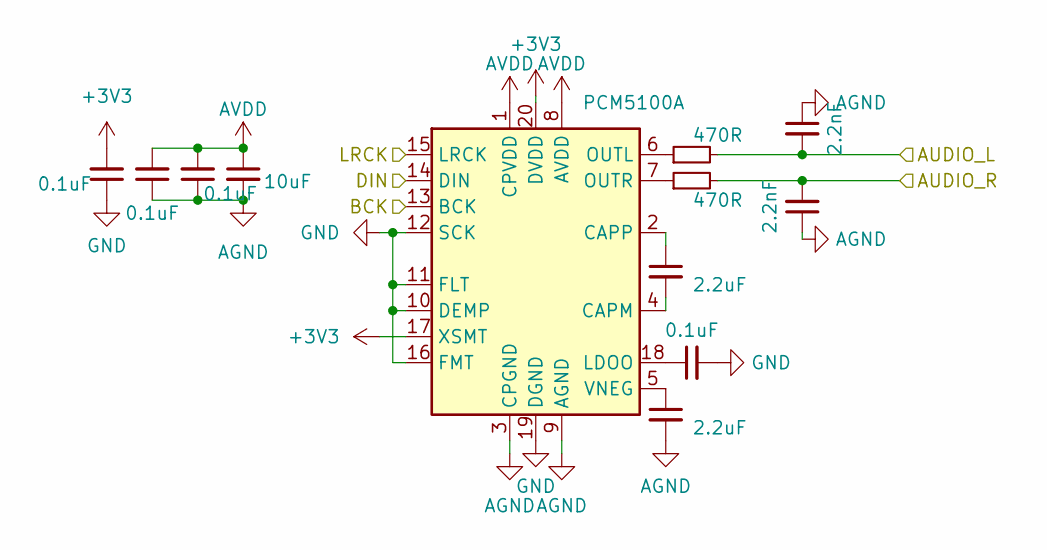
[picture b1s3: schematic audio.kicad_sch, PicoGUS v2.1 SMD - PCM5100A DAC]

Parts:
C14, C15, C16, C20: 0.1uF; C_0805_2012Metric_Pad1.18x1.45mm_HandSolder; MPN CL21B104KBCNNNC; DigiKey 1276-1003-1-ND
C17: 10uF; C_1206_3216Metric_Pad1.33x1.80mm_HandSolder; MPN CL31A106KAHNNNE; DigiKey 1276-1075-1-ND
C18, C19: 2.2uF; C_0805_2012Metric_Pad1.18x1.45mm_HandSolder; MPN C2012X7R1H225K125AC; DigiKey 445-5968-1-ND
C21, C22: 2.2nF; C_0805_2012Metric_Pad1.18x1.45mm_HandSolder; MPN CL21C222JBFNNNE; DigiKey 1276-2993-1-ND
R10, R11: 470R; R_0805_2012Metric_Pad1.20x1.40mm_HandSolder; MPN RT0805BRD07470RL; DigiKey YAG1904CT-ND
U10: PCM5100A; TSSOP-20_4.4x6.5mm_P0.65mm_HandSolder; MPN PCM5100APWR; DigiKey 296-36705-1-ND

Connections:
+3V3: C14.2, U10.17 (XSMT), U10.20 (DVDD); also elsewhere on the board
AGND: C15.1, C16.1, C17.2, C19.2, C21.1, C22.1, U10.3 (CPGND), U10.9 (AGND); also elsewhere on the board
AVDD: C15.2, C16.2, C17.1, U10.1 (CPVDD), U10.8 (AVDD); also elsewhere on the board
BCK: U10.13 (BCK); also elsewhere on the board
DIN: U10.14 (DIN); also elsewhere on the board
GND: C14.1, C20.2, U10.10 (DEMP), U10.11 (FLT), U10.12 (SCK), U10.16 (FMT), U10.19 (DGND); also elsewhere on the board
LRCK: U10.15 (LRCK); also elsewhere on the board
unnamed: C18.2, U10.4 (CAPM)
unnamed: C18.1, U10.2 (CAPP)
unnamed: C20.1, U10.18 (LDOO)
unnamed: R10.1, U10.6 (OUTL)
unnamed: R11.1, U10.7 (OUTR)
unnamed: C19.1, U10.5 (VNEG)
PGAUDIO_L: C21.2, R10.2; also elsewhere on the board
PGAUDIO_R: C22.2, R11.2; also elsewhere on the board

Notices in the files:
hw-smd-v2.1/PicoGUS-SMD.kicad_pcb:
© 2023-2026 Ian Scott (polpo),
Licensed under CERN-OHL-P v2
hw-tht-v1.3/PicoGUS-THT.kicad_pcb:
© 2023-2026 Ian Scott (polpo), Vidar Waagbø (waagbo)
